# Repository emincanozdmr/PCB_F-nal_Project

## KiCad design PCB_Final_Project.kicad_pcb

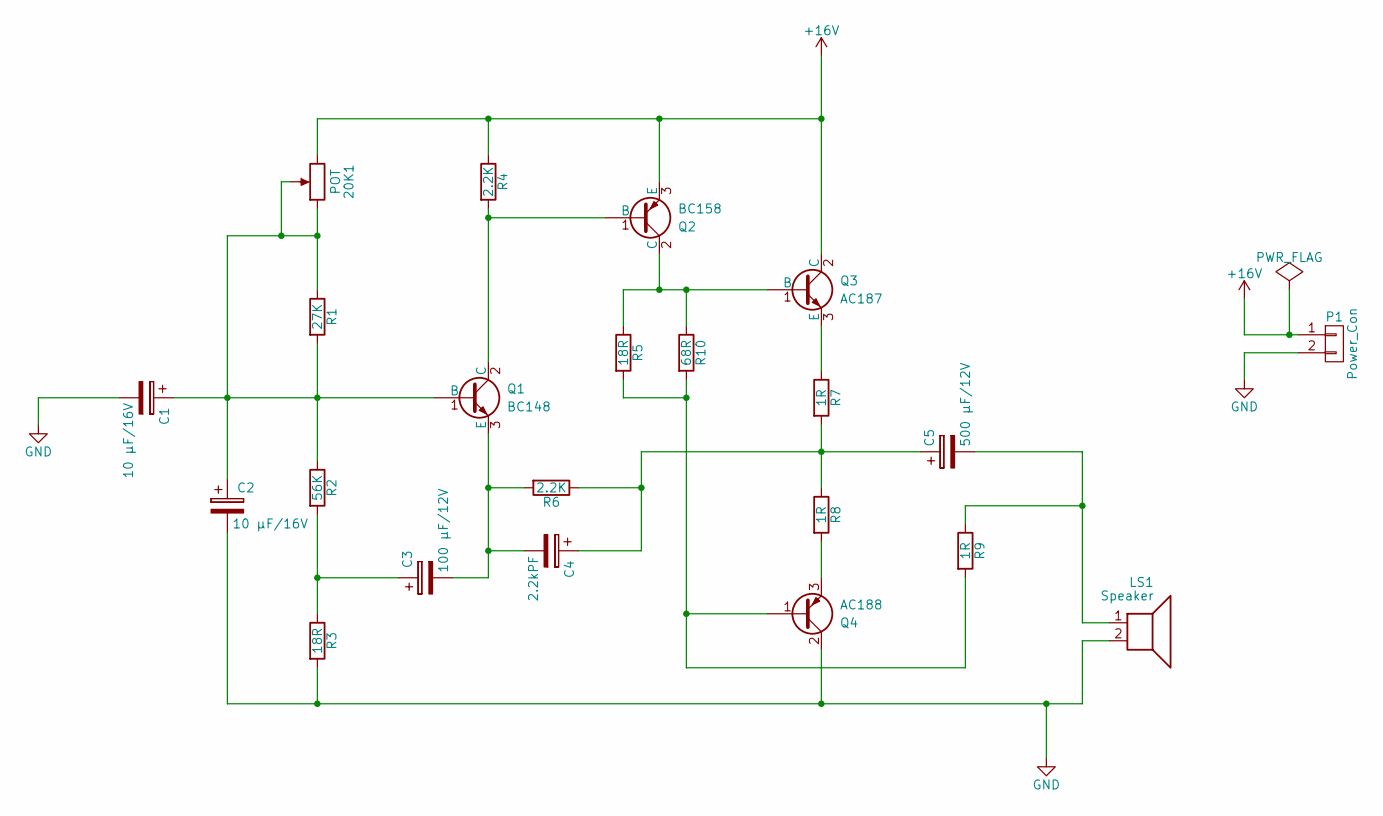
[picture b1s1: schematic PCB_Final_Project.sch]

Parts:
20K1: POT; Potentiometer_Alps_RK097_Single_Vertical
C1, C2: 10 µF/16V; CP_Axial_L10.0mm_D4.5mm_P15.00mm_Horizontal
C3: 100 µF/12V; CP_Axial_L10.0mm_D4.5mm_P15.00mm_Horizontal
C4: 2.2kPF; CP_Axial_L10.0mm_D4.5mm_P15.00mm_Horizontal
C5: 500 µF/12V; CP_Axial_L10.0mm_D4.5mm_P15.00mm_Horizontal
LS1: Speaker; RV_Disc_D12_W3.9_P7.5
P1: Power_Con; Banana_Jack_2Pin
Q1: BC148; TO-92_Molded_Narrow
Q2: BC158; TO-92_Molded_Narrow
Q3: AC187; TO-11-3
Q4: AC188; TO-11-3
R1: 27K; R_Axial_DIN0204_L3.6mm_D1.6mm_P5.08mm_Horizontal
R2: 56K; R_Axial_DIN0204_L3.6mm_D1.6mm_P5.08mm_Horizontal
R3, R5: 18R; R_Axial_DIN0204_L3.6mm_D1.6mm_P5.08mm_Horizontal
R4, R6: 2.2K; R_Axial_DIN0204_L3.6mm_D1.6mm_P5.08mm_Horizontal
R7, R8, R9: 1R; R_Axial_DIN0204_L3.6mm_D1.6mm_P5.08mm_Horizontal
R10: 68R; R_Axial_DIN0204_L3.6mm_D1.6mm_P5.08mm_Horizontal

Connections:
+16V: 20K1.3, P1.1, Q2.3 (E), Q3.2 (C), R4.1
GND: C1.2, C2.2, LS1.2, P1.2, Q4.2 (C), R3.2
unnamed: 20K1.1, 20K1.2, C1.1, C2.1, Q1.1 (B), R1.1, R1.2, R2.1
unnamed: C3.1, R2.2, R3.1
unnamed: C3.2, C4.2, Q1.3 (E), R6.2
unnamed: C4.1, C5.1, R6.1, R7.2, R8.1
unnamed: C5.2, LS1.1, R9.1
unnamed: Q1.2 (C), Q2.1 (B), R4.2
unnamed: Q2.2 (C), Q3.1 (B), R5.1, R10.1
unnamed: Q3.3 (E), R7.1
unnamed: Q4.1 (B), R5.2, R9.2, R10.2
unnamed: Q4.3 (E), R8.2

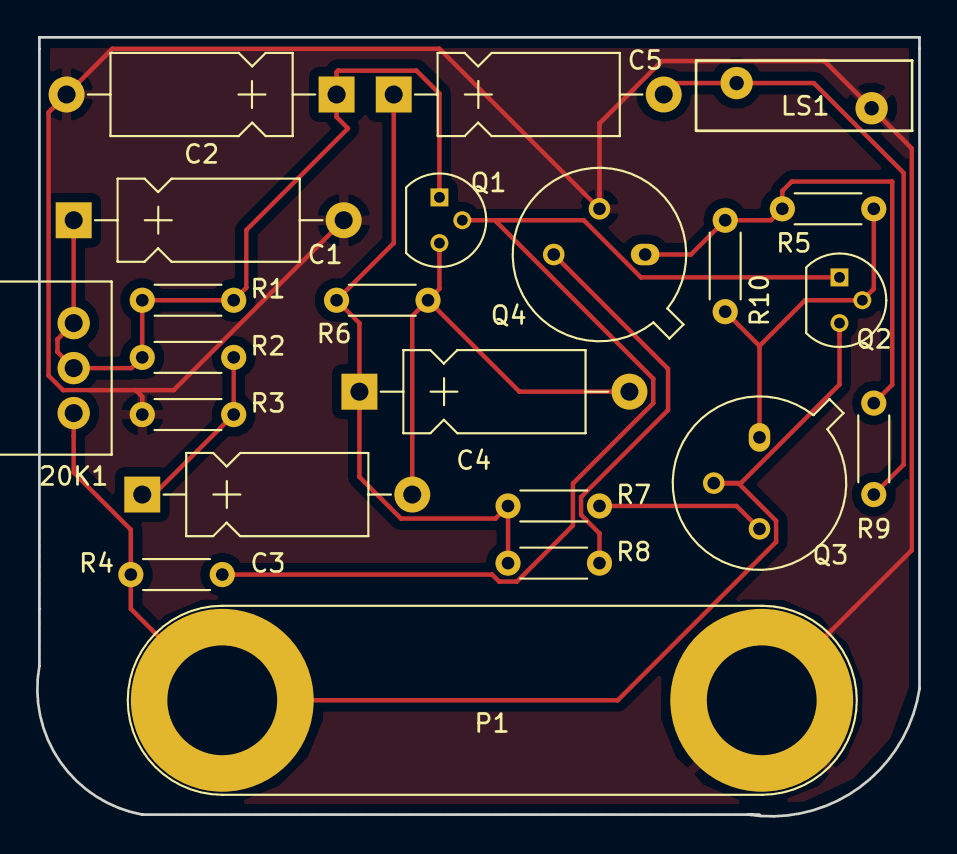
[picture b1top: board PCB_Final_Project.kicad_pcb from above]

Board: 2 copper layers, 49.0 x 43.3 mm, 22 parts (0 on the bottom side), 12 nets.

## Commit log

2017-06-07 Final Project
